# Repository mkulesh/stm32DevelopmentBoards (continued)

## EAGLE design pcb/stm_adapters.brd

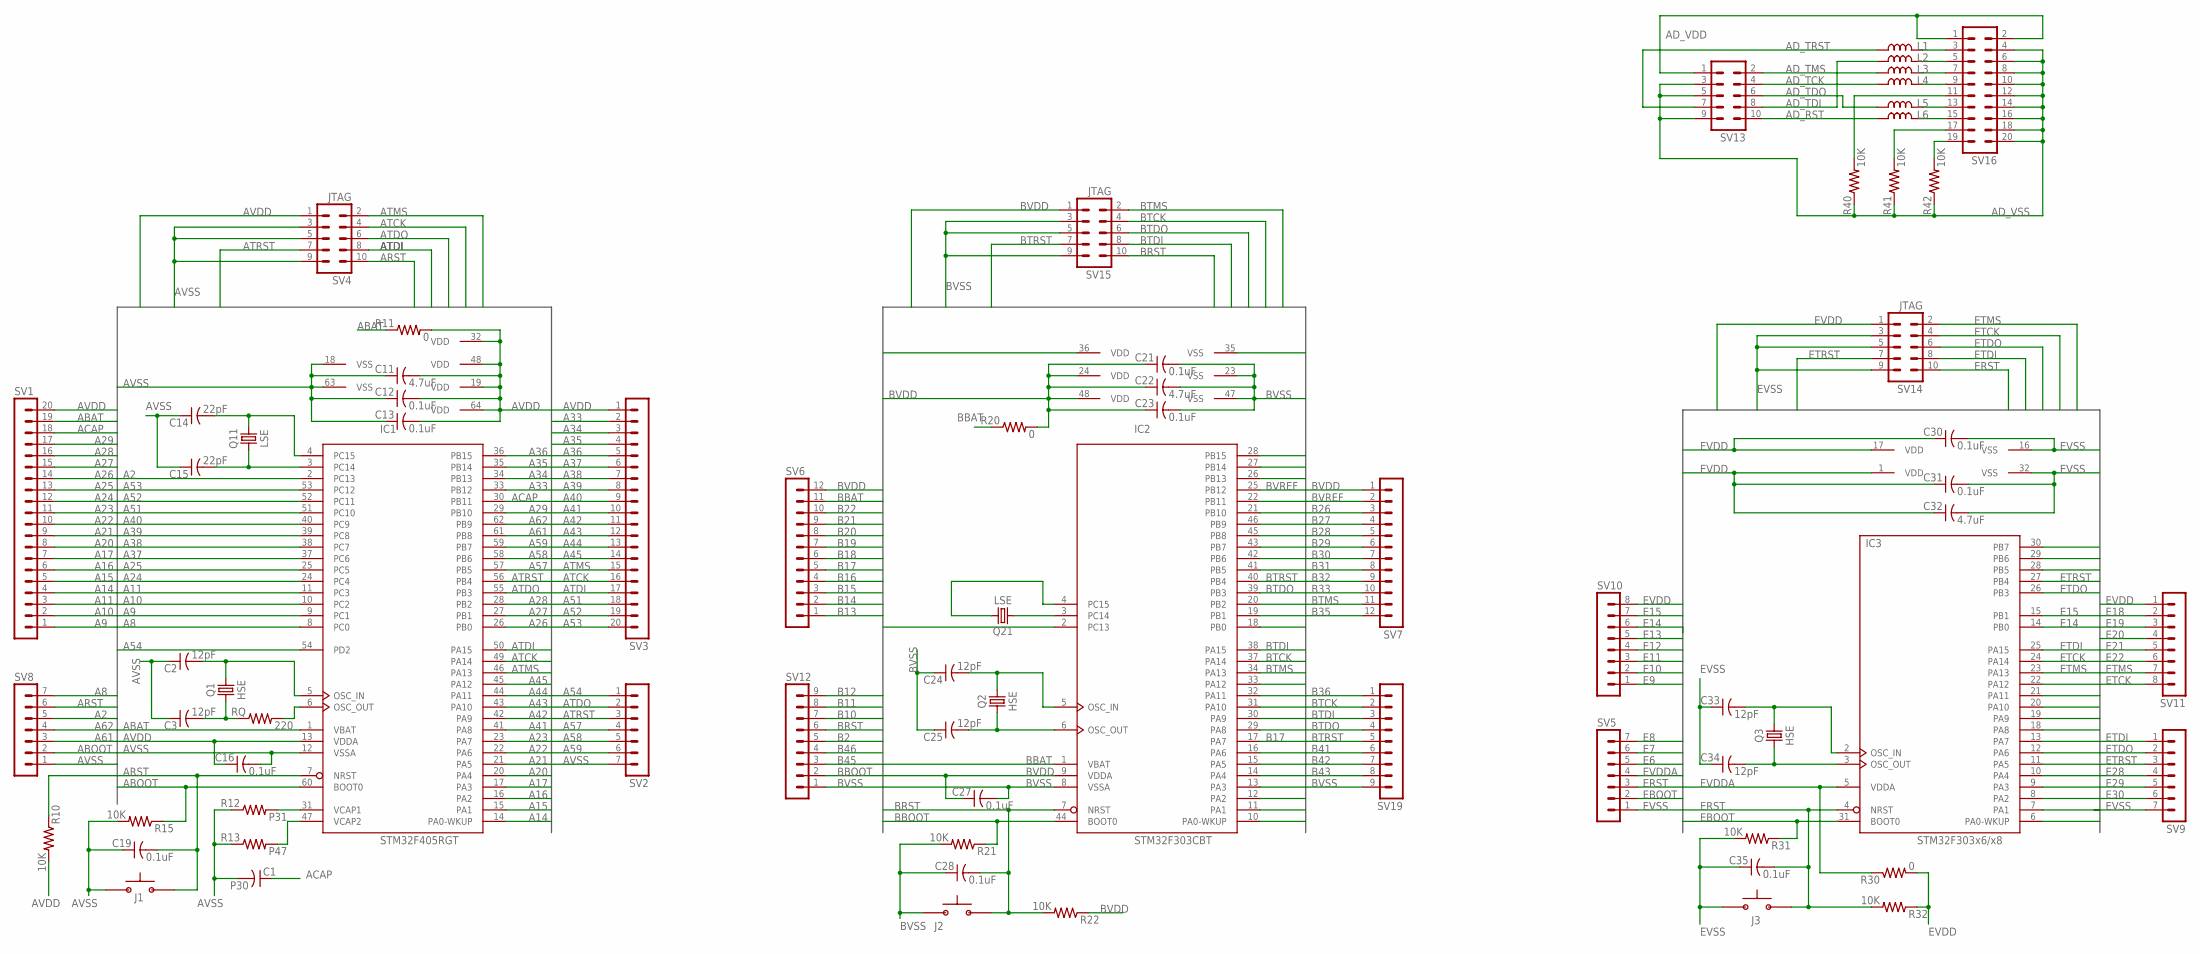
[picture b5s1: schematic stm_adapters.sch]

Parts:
C1: P30; C0805
C2, C3, C24, C25, C33, C34: 12pF; C0805
C11, C22, C32: 4.7uF; C0805
C12, C13, C16, C19, C21, C23, C27, C28, C30, C31, C35: 0.1uF; C0805
C14, C15: 22pF; C0805
IC1: STM32F405RGT; LQFP64
IC2: STM32F303CBT; LQFP48
IC3: STM32F303x6/x8; LQFP32
J1, J2, J3: BUTTON-FSM14JRT
L1, L2, L3, L4, L5, L6: L-USL0603; L0603
Q1, Q2, Q3: HSE; Q-HC-46X
Q11, Q21: LSE; Q-MC-306
R10, R15, R21, R22, R31, R32, R40, R41, R42: 10K; R0805
R11, R20, R30: 0; R0805
R12: P31; R0805
R13: P47; R0805
RQ: 220; R0805
SV1, SV3: MA20-1NO-PL; MA20-1-NO-PL
SV2, SV5, SV8, SV9: MA07-1NO-PL; MA07-1-NO-PL
SV4, SV14, SV15: JTAG; MA05-2
SV6, SV7: MA12-1NO-PL; MA12-1-NO-PL
SV10, SV11: MA08-1NO-PL; MA08-1-NO-PL
SV12, SV19: MA09-1NO-PL; MA09-1-NO-PL
SV13: MA05-2
SV16: MA10-2

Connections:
A2: IC1.2 (PC13), SV8.5
A8: IC1.8 (PC0), SV8.7
A9: IC1.9 (PC1), SV1.1
A10: IC1.10 (PC2), SV1.2
A11: IC1.11 (PC3), SV1.3
A14: IC1.14 (PA0-WKUP), SV1.4
A15: IC1.15 (PA1), SV1.5
A16: IC1.16 (PA2), SV1.6
A17: IC1.17 (PA3), SV1.7
A20: IC1.20 (PA4), SV1.8
A21: IC1.21 (PA5), SV1.9
A22: IC1.22 (PA6), SV1.10
A23: IC1.23 (PA7), SV1.11
A24: IC1.24 (PC4), SV1.12
A25: IC1.25 (PC5), SV1.13
A26: IC1.26 (PB0), SV1.14
A27: IC1.27 (PB1), SV1.15
A28: IC1.28 (PB2), SV1.16
A29: IC1.29 (PB10), SV1.17
A33: IC1.33 (PB12), SV3.2
A34: IC1.34 (PB13), SV3.3
A35: IC1.35 (PB14), SV3.4
A36: IC1.36 (PB15), SV3.5
A37: IC1.37 (PC6), SV3.6
A38: IC1.38 (PC7), SV3.7
A39: IC1.39 (PC8), SV3.8
A40: IC1.40 (PC9), SV3.9
A41: IC1.41 (PA8), SV3.10
A42: IC1.42 (PA9), SV3.11
A43: IC1.43 (PA10), SV3.12
A44: IC1.44 (PA11), SV3.13
A45: IC1.45 (PA12), SV3.14
A51: IC1.51 (PC10), SV3.18
A52: IC1.52 (PC11), SV3.19
A53: IC1.53 (PC12), SV3.20
A54: IC1.54 (PD2), SV2.1
A57: IC1.57 (PB5), SV2.4
A58: IC1.58 (PB6), SV2.5
A59: IC1.59 (PB7), SV2.6
A61: IC1.61 (PB8), SV8.3
A62: IC1.62 (PB9), SV8.4
ABAT: IC1.1 (VBAT), R11.1, SV1.19
ABOOT: IC1.60 (BOOT0), R15.1, SV8.2
ACAP: C1.1, IC1.30 (PB11), SV1.18
ACAP1: IC1.31 (VCAP1), R12.2
ACAP2: IC1.47 (VCAP2), R13.2
AD_RST: L6.1, SV13.10
AD_TCK: L4.1, SV13.4
AD_TDI: L2.1, SV13.8
AD_TDO: L5.1, SV13.6
AD_TMS: L3.1, SV13.2
AD_TRST: L1.1, SV13.7
AD_VDD: SV13.1, SV16.1, SV16.2
AD_VSS: R40.1, R41.1, R42.1, SV13.3, SV13.5, SV13.9, SV16.4, SV16.6, SV16.8, SV16.10, SV16.12, SV16.14, SV16.16, SV16.18, SV16.20
ARST: C19.2, IC1.7 (NRST), J1.P$2 (2), R10.1, SV4.10, SV8.6
ATCK: IC1.49 (PA14), SV3.16, SV4.4
ATDI: IC1.50 (PA15), SV3.17, SV4.8
ATDO: IC1.55 (PB3), SV2.2, SV4.6
ATMS: IC1.46 (PA13), SV3.15, SV4.2
ATRST: IC1.56 (PB4), SV2.3, SV4.7
AVDD: C11.2, C12.2, C13.2, C16.1, IC1.13 (VDDA), IC1.19 (VDD), IC1.32 (VDD), IC1.48 (VDD), IC1.64 (VDD), R10.2, R11.2, SV1.20, SV3.1, SV4.1
AVSS: C1.2, C2.1, C3.1, C11.1, C12.1, C13.1, C14.1, C15.1, C16.2, C19.1, IC1.12 (VSSA), IC1.18 (VSS), IC1.63 (VSS), J1.P$1 (1), R12.1, R13.1, R15.2, SV2.7, SV4.3, SV4.5, SV4.9, SV8.1
B2: IC2.2 (PC13), SV12.5
B10: IC2.10 (PA0-WKUP), SV12.7
B11: IC2.11 (PA1), SV12.8
B12: IC2.12 (PA2), SV12.9
B13: IC2.13 (PA3), SV6.1
B14: IC2.14 (PA4), SV6.2
B15: IC2.15 (PA5), SV6.3
B16: IC2.16 (PA6), SV6.4
B17: IC2.17 (PA7), SV6.5
B18: IC2.18 (PB0), SV6.6
B19: IC2.19 (PB1), SV6.7
B20: IC2.20 (PB2), SV6.8
B21: IC2.21 (PB10), SV6.9
B22: IC2.22 (PB11), SV6.10
B26: IC2.26 (PB13), SV7.3
B27: IC2.27 (PB14), SV7.4
B28: IC2.28 (PB15), SV7.5
B29: IC2.29 (PA8), SV7.6
B30: IC2.30 (PA9), SV7.7
B31: IC2.31 (PA10), SV7.8
B32: IC2.32 (PA11), SV7.9
B33: IC2.33 (PA12), SV7.10
B35: IC2.35 (VSS), SV7.12
B36: IC2.36 (VDD), SV19.1
B41: IC2.41 (PB5), SV19.6
B42: IC2.42 (PB6), SV19.7
B43: IC2.43 (PB7), SV19.8
B45: IC2.45 (PB8), SV12.3
B46: IC2.46 (PB9), SV12.4
BBAT: IC2.1 (VBAT), R20.1, SV6.11
BBOOT: IC2.44 (BOOT0), R21.1, SV12.2
BRST: C28.2, IC2.7 (NRST), J2.P$2 (2), R22.2, SV12.6, SV15.10
BTCK: IC2.37 (PA14), SV15.4, SV19.2
BTDI: IC2.38 (PA15), SV15.8, SV19.3
BTDO: IC2.39 (PB3), SV15.6, SV19.4
BTMS: IC2.34 (PA13), SV7.11, SV15.2
BTRST: IC2.40 (PB4), SV15.7, SV19.5
BVDD: C21.1, C22.1, C23.1, C27.1, IC2.9 (VDDA), IC2.24 (VDD), IC2.48 (VDD), R20.2, R22.1, SV6.12, SV7.1, SV15.1
BVREF: IC2.25 (PB12), SV7.2
BVSS: C21.2, C22.2, C23.2, C24.1, C25.1, C27.2, C28.1, IC2.8 (VSSA), IC2.23 (VSS), IC2.47 (VSS), J2.P$1 (1), R21.2, SV12.1, SV15.3, SV15.5, SV15.9, SV19.9
E6: IC3.6 (PA0-WKUP), SV5.5
E7: IC3.7 (PA1), SV5.6
E8: IC3.8 (PA2), SV5.7
E9: IC3.9 (PA3), SV10.1
E10: IC3.10 (PA4), SV10.2
E11: IC3.11 (PA5), SV10.3
E12: IC3.12 (PA6), SV10.4
E13: IC3.13 (PA7), SV10.5
E14: IC3.14 (PB0), SV10.6
E15: IC3.15 (PB1), SV10.7
E18: IC3.18 (PA8), SV11.2
E19: IC3.19 (PA9), SV11.3
E20: IC3.20 (PA10), SV11.4
E21: IC3.21 (PA11), SV11.5
E22: IC3.22 (PA12), SV11.6
E28: IC3.28 (PB5), SV9.4
E29: IC3.29 (PB6), SV9.5
E30: IC3.30 (PB7), SV9.6
EBOOT: IC3.31 (BOOT0), R31.1, SV5.2
ERST: C35.2, IC3.4 (NRST), J3.P$2 (2), R32.2, SV5.3, SV14.10
ETCK: IC3.24 (PA14), SV11.8, SV14.4
ETDI: IC3.25 (PA15), SV9.1, SV14.8
ETDO: IC3.26 (PB3), SV9.2, SV14.6
ETMS: IC3.23 (PA13), SV11.7, SV14.2
ETRST: IC3.27 (PB4), SV9.3, SV14.7
EVDD: C30.1, C31.1, C32.1, IC3.1 (VDD), IC3.17 (VDD), R30.2, R32.1, SV10.8, SV11.1, SV14.1
EVDDA: IC3.5 (VDDA), R30.1, SV5.4
EVSS: C30.2, C31.2, C32.2, C33.1, C34.1, C35.1, IC3.16 (VSS), IC3.32 (VSS), J3.P$1 (1), R31.2, SV5.1, SV9.7, SV14.3, SV14.5, SV14.9
unnamed: R42.2, SV16.19
unnamed: R41.2, SV16.17
unnamed: R40.2, SV16.11
unnamed: L6.2, SV16.15
unnamed: L5.2, SV16.13
unnamed: L4.2, SV16.9
unnamed: C24.2, IC2.5 (OSC_IN), Q2.1
unnamed: C25.2, IC2.6 (OSC_OUT), Q2.2
unnamed: L3.2, SV16.7
unnamed: IC2.3 (PC14), Q21.1
unnamed: IC2.4 (PC15), Q21.4 (2)
unnamed: L2.2, SV16.5
unnamed: L1.2, SV16.3
unnamed: C34.2, IC3.3 (OSC_OUT), Q3.1
unnamed: C33.2, IC3.2 (OSC_IN), Q3.2
unnamed: C15.2, IC1.3 (PC14), Q11.1
unnamed: C14.2, IC1.4 (PC15), Q11.4 (2)
unnamed: C2.2, IC1.5 (OSC_IN), Q1.1
unnamed: IC1.6 (OSC_OUT), RQ.2
unnamed: C3.2, Q1.2, RQ.1

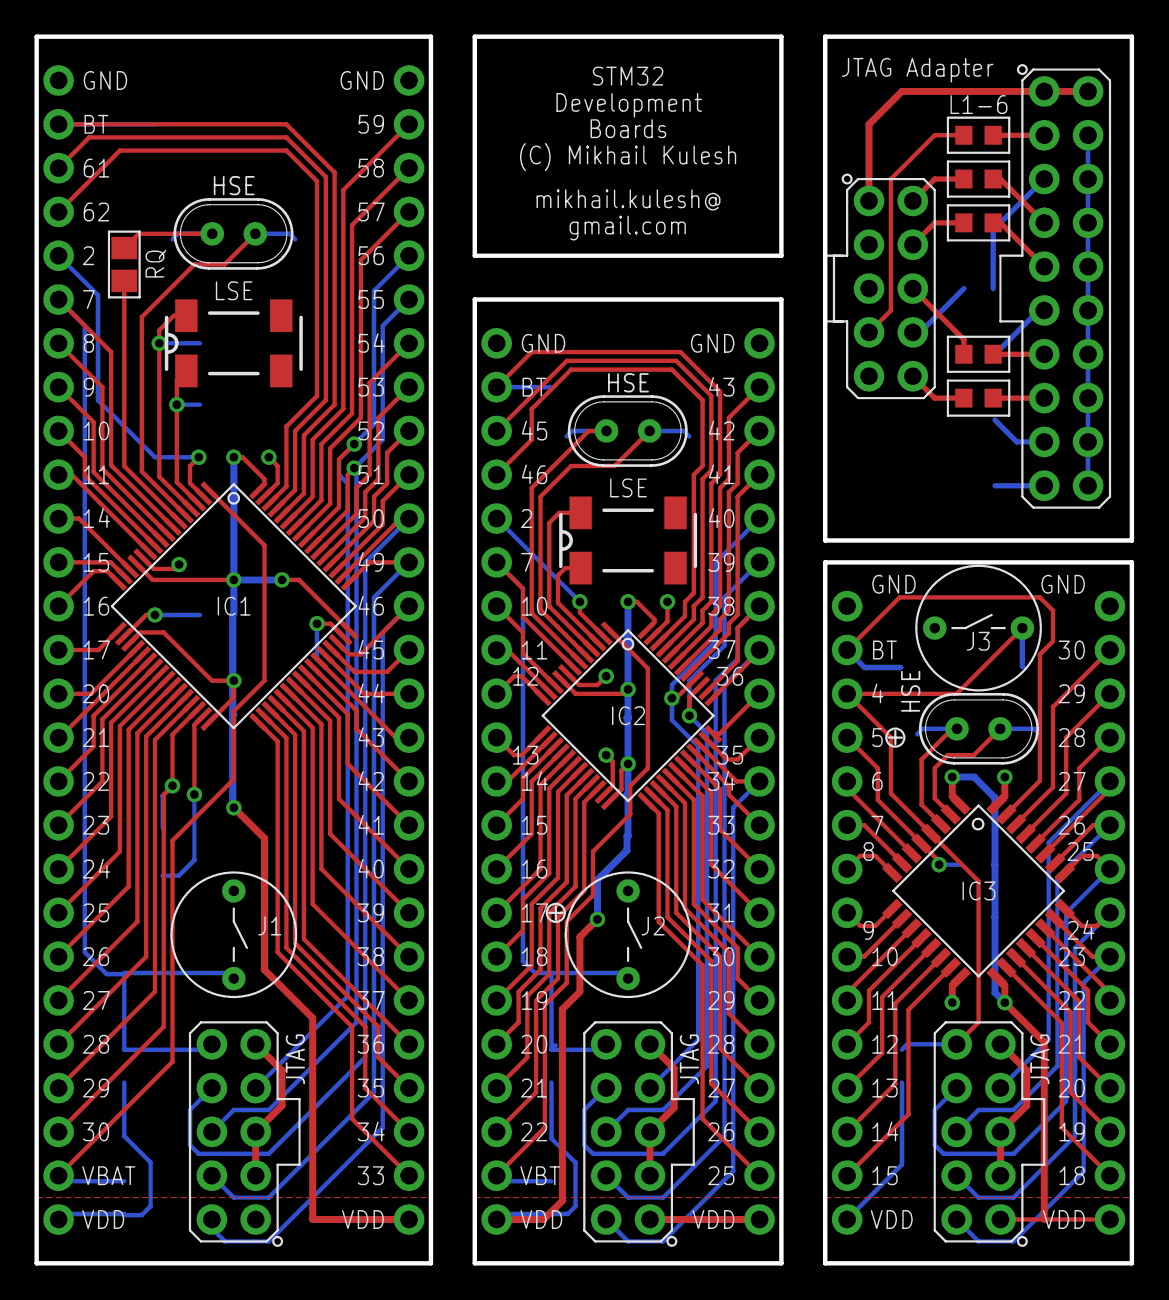
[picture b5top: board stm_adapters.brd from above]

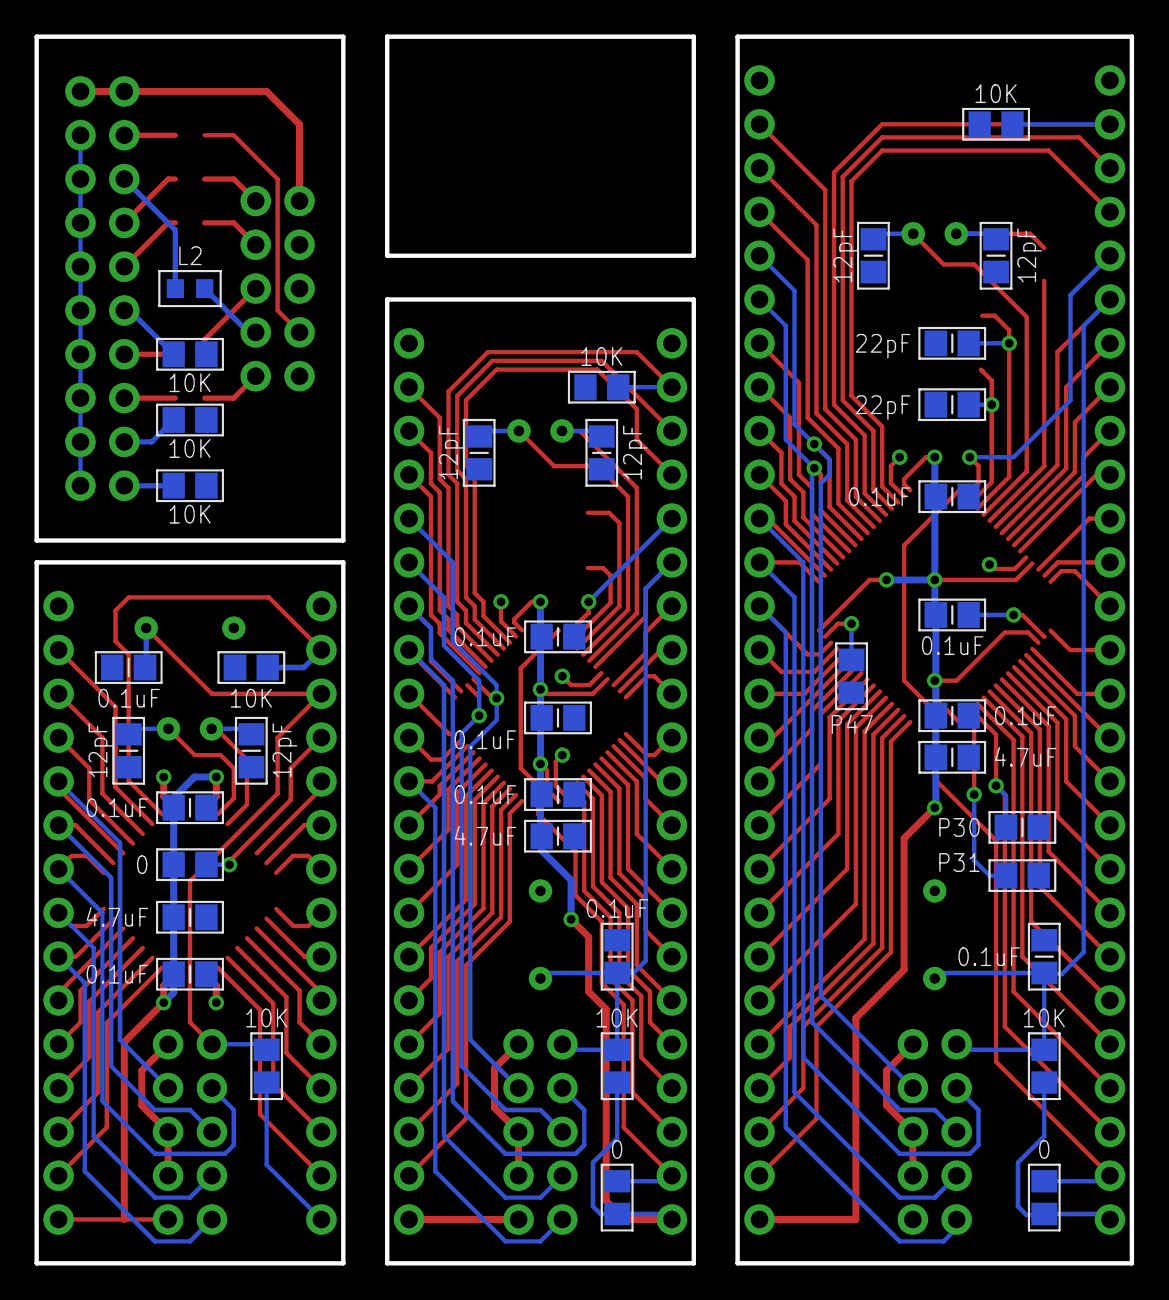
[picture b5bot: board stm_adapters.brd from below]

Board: 2 copper layers, 63.5 x 71.1 mm, 72 parts (50 on the bottom side), 150 nets.

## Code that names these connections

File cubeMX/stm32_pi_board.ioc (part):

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Mcu.Name=STM32F405RGTx
Mcu.Package=LQFP64
Mcu.UserName=STM32F405RGTx
PA1.GPIOParameters=GPIO_Label
PA1.GPIO_Label=ESP-ON
PA1.Signal=GPIO_Output
PA11.Mode=Device_Only
PA11.Signal=USB_OTG_FS_DM
PA12.Mode=Device_Only
PA12.Signal=USB_OTG_FS_DP
PA13.Mode=Serial-Wire
PA13.Signal=SYS_JTMS-SWDIO
PA14.Mode=Serial-Wire
PA14.Signal=SYS_JTCK-SWCLK
PA15.GPIOParameters=GPIO_Label
PA15.GPIO_Label=SD-ON
PA15.Signal=GPIO_Output
PA2.GPIOParameters=GPIO_Label
PA2.GPIO_Label=ESP-TX
PA2.Mode=Asynchronous
PA2.Signal=USART2_TX
PA3.GPIOParameters=GPIO_Label
PA3.GPIO_Label=ESP-RX
PA3.Mode=Asynchronous
PA3.Signal=USART2_RX
PA4.Signal=GPXTI4
PA5.Mode=Full_Duplex_Slave
PA5.Signal=SPI1_SCK
PA6.Mode=Full_Duplex_Slave
PA6.Signal=SPI1_MISO
PA7.Mode=Full_Duplex_Slave
PA7.Signal=SPI1_MOSI
PA8.Mode=Clock-out-1
PA8.Signal=RCC_MCO_1
PA9.Mode=Activate_VBUS
PA9.Signal=USB_OTG_FS_VBUS
PB10.GPIOParameters=GPIO_Label
PB10.GPIO_Label=AUD-BCK
PB10.Mode=Half_Duplex_Slave
PB10.Signal=I2S2_CK
PB11.GPIOParameters=GPIO_Label
PB11.GPIO_Label=AUD-ON
PB11.Signal=GPIO_Output
PB12.GPIOParameters=GPIO_Label
PB12.GPIO_Label=AUD-WS
PB12.Mode=Half_Duplex_Slave
PB12.Signal=I2S2_WS
PB13.GPIOParameters=GPIO_Label
PB13.GPIO_Label=AUD-MUTE
PB13.Signal=GPIO_Output
PB14.GPIOParameters=GPIO_Label
PB14.GPIO_Label=AUD-SMPL
PB14.Signal=GPIO_Output
PB15.GPIOParameters=GPIO_Label
PB15.GPIO_Label=AUD-DAT
PB15.Mode=Half_Duplex_Slave
PB15.Signal=I2S2_SD
PB3.GPIOParameters=GPIO_Label
PB3.GPIO_Label=SD-DET
PB3.Signal=GPIO_Input
PB6.Mode=Asynchronous
PB6.Signal=USART1_TX
PB7.Mode=Asynchronous
PB7.Signal=USART1_RX
PC1.GPIOParameters=GPIO_Label
PC1.GPIO_Label=D1_GREEN
PC1.Signal=GPIO_Output
PC10.Mode=SD_4_bits_Wide_bus
PC10.Signal=SDIO_D2
PC11.Mode=SD_4_bits_Wide_bus
PC11.Signal=SDIO_D3
PC12.Mode=SD_4_bits_Wide_bus
PC12.Signal=SDIO_CK
PC14-OSC32_IN.Mode=LSE-External-Oscillator
PC14-OSC32_IN.Signal=RCC_OSC32_IN
PC15-OSC32_OUT.Mode=LSE-External-Oscillator
PC15-OSC32_OUT.Signal=RCC_OSC32_OUT
PC2.GPIOParameters=GPIO_Label
PC2.GPIO_Label=D1_BLUE
PC2.Signal=GPIO_Output
PC3.GPIOParameters=GPIO_Label
PC3.GPIO_Label=D1_RED
PC3.Signal=GPIO_Output
PC8.Mode=SD_4_bits_Wide_bus
PC8.Signal=SDIO_D0
PC9.Mode=SD_4_bits_Wide_bus
PC9.Signal=SDIO_D1
PD2.Mode=SD_4_bits_Wide_bus
PD2.Signal=SDIO_CMD
PH0-OSC_IN.Mode=HSE-External-Oscillator
PH0-OSC_IN.Signal=RCC_OSC_IN
PH1-OSC_OUT.Mode=HSE-External-Oscillator
PH1-OSC_OUT.Signal=RCC_OSC_OUT
RCC.HSE_VALUE=16000000
RCC.SYSCLKFreq_VALUE=64000000
RCC.SYSCLKSource=RCC_SYSCLKSOURCE_PLLCLK

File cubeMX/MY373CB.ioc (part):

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Mcu.Name=STM32F373C(8-B-C)Tx
Mcu.Package=LQFP48
Mcu.UserName=STM32F373CBTx
PA8.Mode=Clock-out
PA8.Signal=RCC_MCO
PB0.Signal=GPIO_Output
PB1.Signal=GPIO_Output
PB6.Mode=Asynchronous
PB6.Signal=USART1_TX
PB7.Mode=Asynchronous
PB7.Signal=USART1_RX
PC14-OSC32_IN.Mode=LSE-External-Oscillator
PC14-OSC32_IN.Signal=RCC_OSC32_IN
PC15-OSC32_OUT.Mode=LSE-External-Oscillator
PC15-OSC32_OUT.Signal=RCC_OSC32_OUT
PF0-OSC_IN.Mode=HSE-External-Oscillator
PF0-OSC_IN.Signal=RCC_OSC_IN
PF1-OSC_OUT.Mode=HSE-External-Oscillator
PF1-OSC_OUT.Signal=RCC_OSC_OUT
RCC.HSEPLLFreq_Value=8000000
RCC.HSE_VALUE=16000000
RCC.SYSCLKFreq_VALUE=72000000
RCC.SYSCLKSource=RCC_SYSCLKSOURCE_PLLCLK

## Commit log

2017-08-25 Added more images
2017-08-25 Added version 2 of the boards
2017-08-25 Added demo/test programs for the boards
2017-09-12 Added .gitignore
2017-09-29 Early drop for STM32PiBoard
2017-10-01 Imprved stm32_pi_board
2017-10-02 STM32-Pi Board submitted to factory
2017-10-17 Added example for STM32-Pi Board
2017-10-18 Added instruction how to flash firmware on ESP-11
2017-10-19 Tested ESP11 module
2017-10-19 Added configuration example
2017-10-20 Fixed minor layout bugs
2017-10-23 Clock configuraton collected in a seprate structure
2017-10-26 Updated PCB
2017-11-09 Revision 1.1 submitted to factory
2018-02-24 Updated photos
2018-03-05 Introduced EspSender
2018-03-06 Implementes message containing pin state
2018-03-12 Expanded configuration and message
2018-04-05 Added driver for audio DAC UDA1334
2018-04-08 Implemented WAV-file player using I2S bus
2018-04-19 Refactored EspSender
2018-04-24 EspSender: process messages asynchroniously
2018-04-24 EspSender: processing of input messages
2018-04-26 EspSender: processing NTP messages
2018-04-27 Refactored Esp11
2018-05-03 Assembled board 1.2
2018-05-04 Updated photo and ESP firmware
2018-05-07 Updated schematic
2018-05-07 Expanded real time clock
2018-05-07 Real time clock is used in ESP
2018-05-11 Expanded configuration
2018-05-11 Improved ESP sender
2018-06-03 Minor code improvements
2018-06-05 Removed BasicIO class
2018-06-05 Introduced hardware layout namespace
2018-06-05 Reworked class System
2018-06-05 Reworked RTC
2018-06-06 Introduced Port and Pin in HardwareLayout
2018-06-07 Introduced HardwareLayout::I2S
2018-06-08 Renames some attributes
2018-06-08 Alternative flag moved to pins
2018-06-08 Improved USART
2018-06-08 Introduced DMA
2018-06-08 Introduced ADC
2018-06-11 Renamed Dma
2018-06-12 Reworked timers
2018-06-13 Introduced SPI
2018-06-14 Removed unused interrupts
2018-06-14 Improved Spi
2018-06-14 Spi using DMA
2018-06-18 Asynchrone logger
2018-06-18 Introduced SharedDevice
2018-06-21 Asynchron ADC
2018-06-22 Refactored DMA usage
2018-06-25 New version of pi_board
2018-06-25 Improved DAC
2018-06-26 Added LMT86
2018-07-01 PCB revision 1.3
2018-07-08 Revision 1.3 of Stm32-Pi-Board
2018-07-27 Updated STM32 adapters
2018-08-01 Submitted PiBoard v1.3
2018-08-26 Updated BOM
2019-04-28 Updated cubeMX model
2021-04-05 moved cubeMX files
2023-07-21 Added description
